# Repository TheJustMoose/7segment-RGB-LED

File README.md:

More photos here:
https://www.instagram.com/p/COdSCiZrfur/

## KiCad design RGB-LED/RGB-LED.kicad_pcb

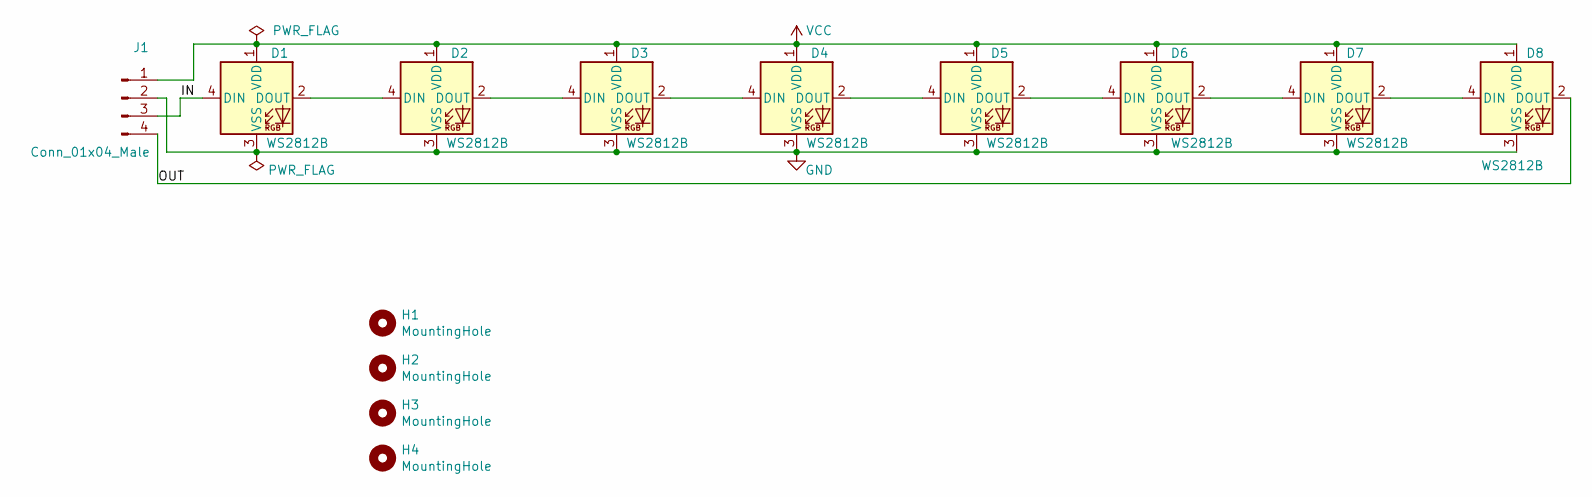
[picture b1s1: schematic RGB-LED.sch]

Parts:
D1, D2, D3, D4, D5, D6, D7, D8: WS2812B; LED_WS2812B_PLCC4_5.0x5.0mm_P3.2mm
H1, H2, H3, H4: MountingHole; MountingHole_2.5mm
J1: Conn_01x04_Male; PinHeader_1x04_P2.54mm_Vertical

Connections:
/IN: D1.4 (DIN), J1.3
/OUT: D8.2 (DOUT), J1.4
GND: D1.3 (VSS), D2.3 (VSS), D3.3 (VSS), D4.3 (VSS), D5.3 (VSS), D6.3 (VSS), D7.3 (VSS), D8.3 (VSS), J1.2
unnamed: D1.2 (DOUT), D2.4 (DIN)
unnamed: D2.2 (DOUT), D3.4 (DIN)
unnamed: D3.2 (DOUT), D4.4 (DIN)
unnamed: D4.2 (DOUT), D5.4 (DIN)
unnamed: D5.2 (DOUT), D6.4 (DIN)
unnamed: D6.2 (DOUT), D7.4 (DIN)
unnamed: D7.2 (DOUT), D8.4 (DIN)
VCC: D1.1 (VDD), D2.1 (VDD), D3.1 (VDD), D4.1 (VDD), D5.1 (VDD), D6.1 (VDD), D7.1 (VDD), D8.1 (VDD), J1.1

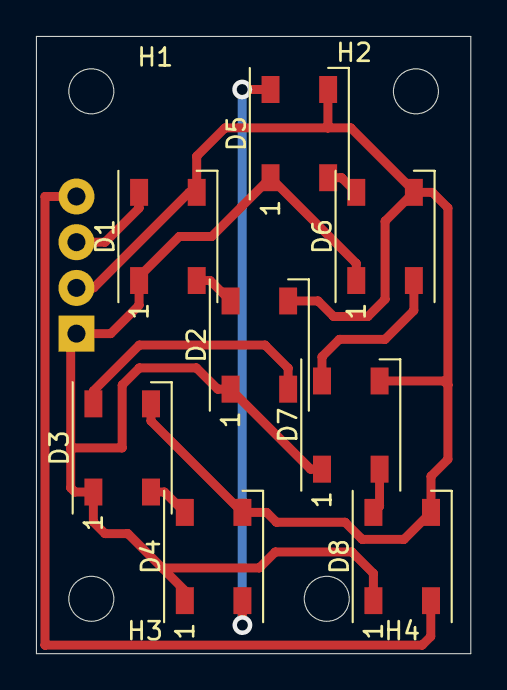
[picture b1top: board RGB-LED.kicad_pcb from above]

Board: 2 copper layers, 24.1 x 34.3 mm, 13 parts (1 on the bottom side), 11 nets.

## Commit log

2021-05-04 7 segment RGB LED. Initial commit.
2021-05-04 readme
